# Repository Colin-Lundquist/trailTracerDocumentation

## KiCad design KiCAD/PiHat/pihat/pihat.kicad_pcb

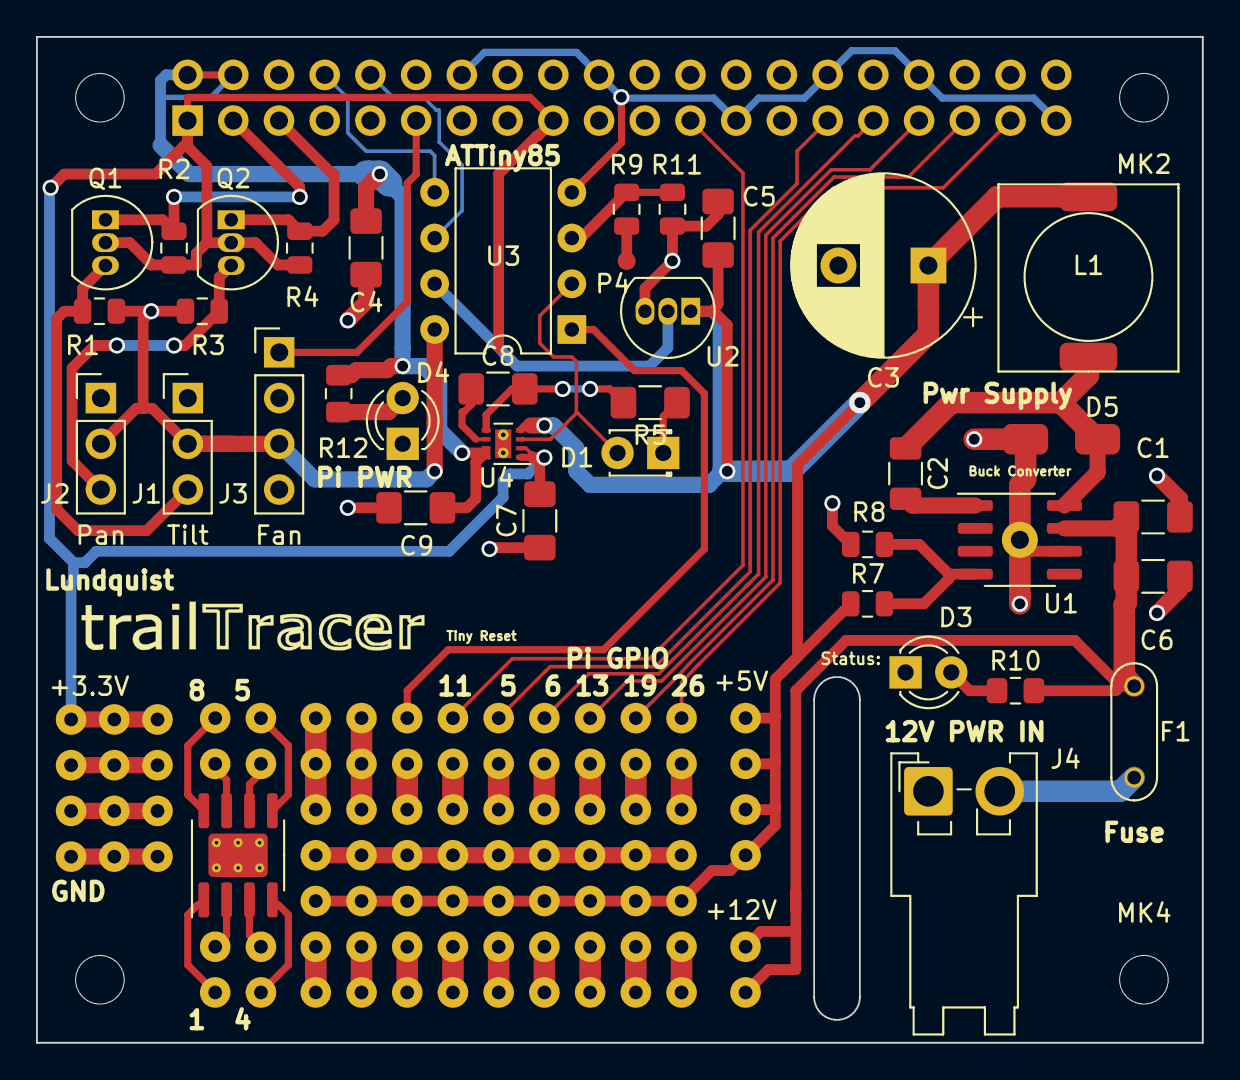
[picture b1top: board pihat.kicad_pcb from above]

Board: 2 copper layers, 64.8 x 55.9 mm, 51 parts (1 on the bottom side), 31 nets.

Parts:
 : Hole
 #2: Hole
 #3,  #4: SOIC_IO
 #5: SOIC-8-1EP_3.9x4.9mm_P1.27mm_EP2.41x3.3mm_Thermal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; SOIC-8-1EP_3.9x4.9mm_P1.27mm_EP2.41x3.3mm_ThermalVias
 #6: Breadbord layout
 #7: M2.5; MountingHole_2.7mm_M2.5
+3.3V, +5V: Hole
+12V: Holes_2
C1, C6: 47 uF; C_1206_3216Metric_Pad1.42x1.75mm_HandSolder
C2: 10 nF; R_1206_3216Metric
C3: 270 uF; CP_Radial_D10.0mm_P5.00mm
C4, C5: 220 uF; C_1206_3216Metric_Pad1.42x1.75mm_HandSolder
C7: 100uF; R_1206_3216Metric_Pad1.42x1.75mm_HandSolder
C8: 220pF; R_1206_3216Metric_Pad1.42x1.75mm_HandSolder
C9: 10uF; R_1206_3216Metric_Pad1.42x1.75mm_HandSolder
D1: LED; LED_D1.8mm_W3.3mm_H2.4mm
D3, D4: LED; LED_D3.0mm
D5: B340
F1: Fuse; Fuse_Holder_TR5
J1: Pan Servo Connector; PinHeader_1x03_P2.54mm_Vertical
J2: Tilt Servo Connector; PinHeader_1x03_P2.54mm_Vertical
J3: Fan; PinHeader_1x04_P2.54mm_Vertical
J4: Power Connector; JST_VH_S2P-VH_1x02_P3.96mm_Horizontal
L1: 15 uH; SRR1050A Coil
MK1, MK2, MK4: M2.5; MountingHole_2.7mm_M2.5
P1: Conn_02x20_Odd_Even; PinSocket_2x20_P2.54mm_Vertical
P4: Pad
Q1, Q2: 2N7000; TO-92_Inline
R1, R2, R3, R4, R11: 10K; R_0805_2012Metric
R5: 220R; R_1206_3216Metric_Pad1.42x1.75mm_HandSolder
R7: 10 KOhm; R_0805_2012Metric
R8: 3.24 KOhm; R_0805_2012Metric
R9: 15K; R_0805_2012Metric
R10: 470; R_0805_2012Metric_Pad1.15x1.40mm_HandSolder
R12: 120R; R_0805_2012Metric_Pad1.15x1.40mm_HandSolder
U1: TPS5430-Q1; SOIC-8-1EP_3.9x4.9mm_P1.27mm_EP2.29x3mm_ThermalVias
U2: LMT87; TO-92_Inline
U3: ATTiny85; DIP-8_W7.62mm
U4: TPS22965; WSON-8-1EP_2x2mm_P0.5mm_EP0.9x1.6mm_ThermalVias

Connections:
+3V3: .1, #2.1, +3.3V.1, C7.2, P1.1, P1.17, Q1.2, Q2.2, R2.2, R4.2, U4.1, U4.2
+5V: .1, #2.1, #6.1, +3.3V.1, +5V.1, C3.1, C5.1, J1.2, J2.2, J3.3, L1.2, R1.2, R3.2, R7.1, U2.1, U3.8, U4.4
+12V: +12V.1, +12V.2, C1.1, C6.1, F1.2, R10.2, U1.7
/GPIO5: #6.1, P1.29
/GPIO6: #6.1, P1.31
/GPIO19(SPI1_MISO): #6.1, P1.35
/GPIO26: #6.1, P1.37
GND: .1, #2.1, #6.1, +3.3V.1, C1.2, C3.2, C4.2, C5.2, C6.2, C7.1, C8.2, C9.1, D3.1, D4.1, D5.2, J1.1, J2.1, J3.4, J4.1, P1.6, P1.9, P1.14, P1.20, P1.25, P1.30, P1.34, P1.39, R5.2, R8.2, R11.2, U1.6, U1.9, U2.3, U3.4, U4.5
GPIO_2: P1.3, Q1.1, R2.1
GPIO_3: P1.5, Q2.1, R4.1
GPIO_11: #6.1, P1.23
GPIO_13: #6.1, P1.33
GPIO_17: J3.1, P1.11
unnamed: C2.1, D5.1, L1.1, U1.8
unnamed: C2.2, U1.1
unnamed: C8.1, U4.6
unnamed: D1.1, R5.1
unnamed: D3.2, R10.1
unnamed: D4.2, R12.1
unnamed: F1.1, J4.2
unnamed: J1.3, Q1.3, R1.1
unnamed: J2.3, Q2.3, R3.1
unnamed: P4.1, R9.2
unnamed: R7.2, R8.1, U1.4
unnamed: R9.1, R11.1, U3.3
unnamed: #6.1, U3.1
PI_5V: C4.1, C9.2, P1.2, P1.4, R12.2, U4.7, U4.8
TINY_B0: P1.8, U3.5
TINY_B1: P1.10, U3.6
TINY_B2: U2.2, U3.7
TINY_B4: D1.2, U3.2, U4.3

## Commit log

2020-02-18 Initial
2020-02-18 compacted servo design
2020-02-18 Added Fan Header
2020-02-24 Temporary Commit
2020-02-28 Minor commit
2020-03-13 Added status LEDs, power relay, organized traces
2020-03-13 Peer review changes
2020-03-13 Professor Drouant feedback
2020-03-19 Revision 1
2020-03-26 Added images
2020-03-26 Added report Rev. 6
2020-04-10 Re-routing of components, fixed bugs from first spin
2020-05-01 Added MOSFET switch, Logo, Prototype area
